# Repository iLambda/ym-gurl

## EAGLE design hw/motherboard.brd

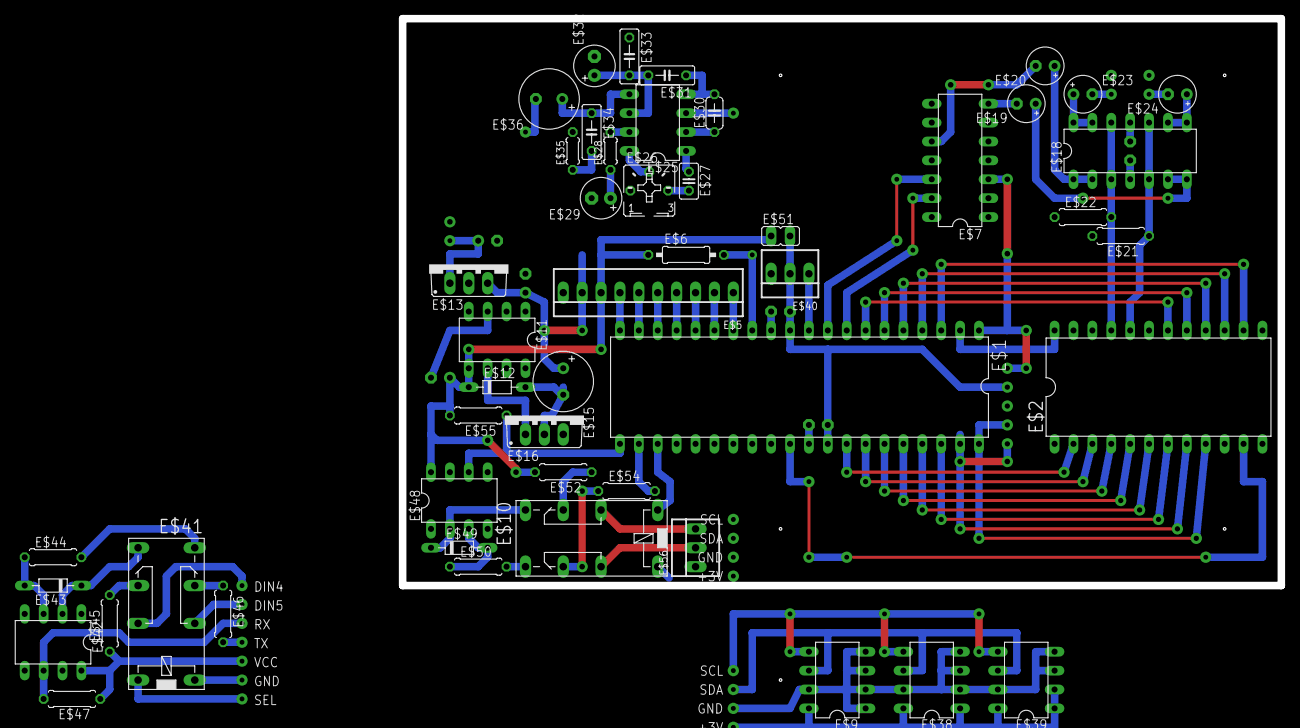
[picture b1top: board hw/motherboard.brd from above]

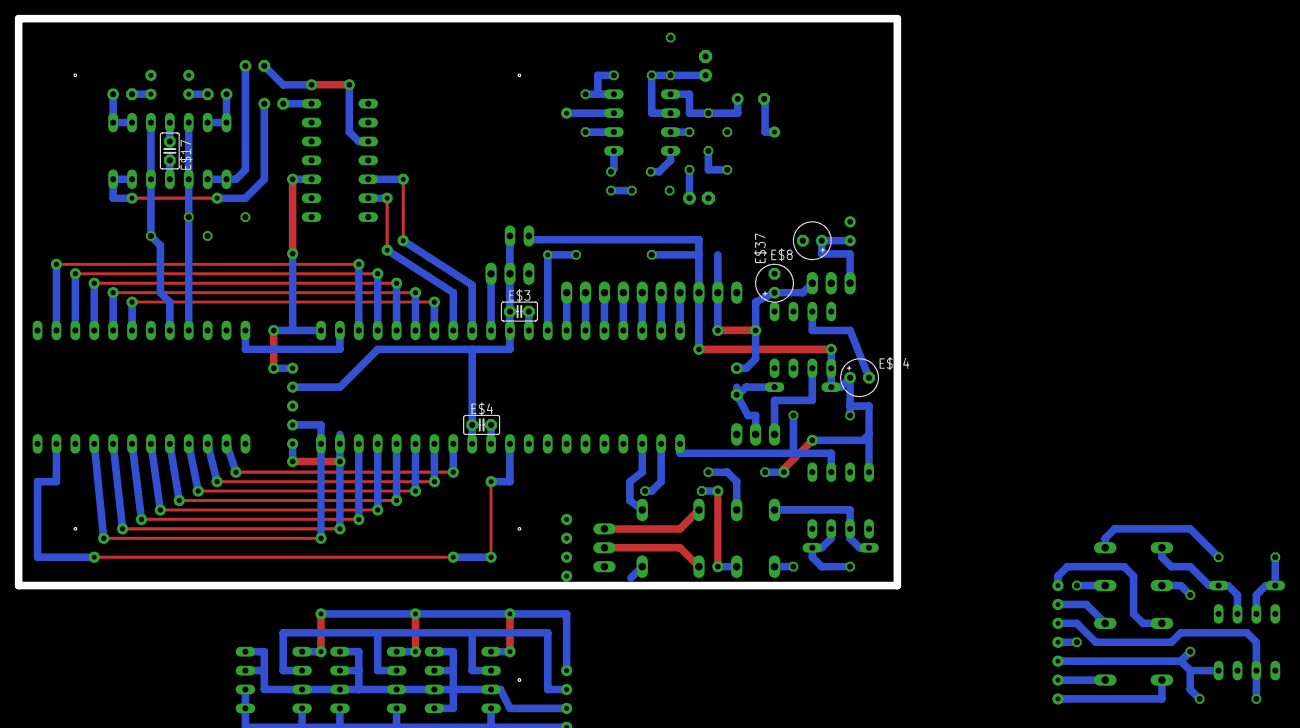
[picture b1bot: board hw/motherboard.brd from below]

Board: 2 copper layers, 118.1 x 76.2 mm, 55 parts (6 on the bottom side), 73 nets.

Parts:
E$1: DIL40
E$2: DIL24-6
E$3, E$4, E$17: C2.5-2
E$5: 22-23-2101
E$6: 0207/10
E$7, E$18: DIL14
E$8, E$14, E$19, E$20, E$23, E$24, E$37: E2,5-5
E$9, E$11, E$25, E$38, E$39, E$42, E$48: DIL08
E$10, E$41: 351
E$12, E$43, E$49: D-7.5
E$13, E$16: TO220V
E$15, E$36: E3,5-8
E$21, E$22, E$44, E$45, E$46, E$47, E$50, E$52, E$54, E$55: 0207/7
E$26: B25P
E$27: C025-025X050
E$28, E$35: 0204/5
E$29, E$32: E2,5-6
E$30: C050-024X044
E$31, E$33, E$34: C050-025X075
E$40, E$56: 22-23-2031
E$51: JP1

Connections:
+3V: E$5.9, E$13.3, E$15.+, E$37.+
+5V: E$5.8, E$6.1, E$11.5, E$12.C, E$14.+, E$48.8, E$51.1, E$52.2, E$55.2
+5V_JMP: E$1.11, E$1.32, E$3.1, E$40.2, E$51.2
GND: E$1.12, E$1.31, E$2.1, E$2.19, E$3.2, E$4.2, E$5.10, E$7.1, E$7.4, E$7.6, E$7.9, E$7.11, E$8.-, E$10.16, E$11.1, E$11.3, E$11.7, E$13.2, E$14.-, E$16.3, E$17.1, E$18.11, E$21.2, E$22.1, E$37.-, E$40.3, E$48.5, E$56.1
S$1: E$7.10, E$20.-
S$2: E$9.8, E$38.1, E$38.8, E$39.1, E$39.2, E$39.8
S$7: E$1.39, E$2.8
S$8: E$1.40, E$2.9
S$9: E$1.33, E$2.2
S$10: E$1.34, E$2.3
S$11: E$1.35, E$2.4
S$12: E$1.36, E$2.5
S$13: E$1.37, E$2.6
S$14: E$1.38, E$2.7
S$15: E$1.14, E$5.1
S$19: E$1.3, E$2.14
S$20: E$1.2, E$2.24
S$22: E$9.5, E$38.5, E$39.5
S$26: E$1.4, E$2.15
S$27: E$1.5, E$2.16
S$28: E$1.6, E$2.17
S$29: E$1.7, E$2.18
S$30: E$1.10, E$40.1
S$35: E$41.O2, E$45.2
S$36: E$1.15, E$5.2
S$37: E$1.16, E$5.3
S$38: E$1.17, E$5.4
S$39: E$1.18, E$5.5
S$40: E$1.19, E$5.6
S$41: E$1.20, E$5.7
S$42: E$1.13, E$6.2
S$43: E$1.21, E$48.6, E$55.1
S$44: E$42.8, E$45.1, E$47.1
S$45: E$41.O1, E$46.1
S$47: E$41.S2, E$42.2, E$43.C
S$49: E$48.3, E$49.A, E$50.1
S$50: E$42.3, E$43.A, E$44.1
S$52: E$10.S1, E$48.2, E$49.C
S$53: E$1.22, E$54.2
S$55: E$1.30, E$2.11
S$56: E$10.S2, E$50.2
S$57: E$41.S1, E$44.2
S$59: E$10.O2, E$54.1
S$63: E$12.A, E$15.-, E$16.2
S$64: E$42.6, E$47.2
S$65: E$1.23, E$10.1
S$66: E$10.P1, E$56.3
S$67: E$10.P2, E$56.2
S$68: E$9.1, E$9.2, E$9.3, E$9.4, E$9.7, E$38.2, E$38.3, E$38.4, E$38.7, E$39.3, E$39.4, E$39.7
S$69: E$10.O1, E$52.1
S$70: E$11.6, E$16.1
S$73: E$18.13, E$18.14, E$23.+
S$74: E$18.1, E$18.2, E$20.+
S$75: E$18.8, E$18.9, E$24.+
S$77: E$1.8, E$7.13
S$78: E$1.9, E$7.12
S$79: E$25.8, E$26.S
S$80: E$1.1, E$7.3
S$82: E$7.7, E$19.-
S$83: E$26.E, E$27.2
S$84: E$2.21, E$18.3, E$18.12, E$22.2
S$85: E$2.20, E$18.5, E$18.10, E$21.1
S$87: E$17.2, E$18.4
S$89: E$18.6, E$18.7, E$19.+
S$93: E$25.7, E$28.2
S$94: E$28.1, E$29.+
S$96: E$25.4, E$30.2, E$31.1
S$97: E$25.2, E$30.1
S$99: E$25.5, E$34.1, E$36.+
S$100: E$25.1, E$27.1
S$101: E$25.6, E$31.2, E$32.+, E$33.2
S$102: E$34.2, E$35.1
S$104: E$8.+, E$13.1

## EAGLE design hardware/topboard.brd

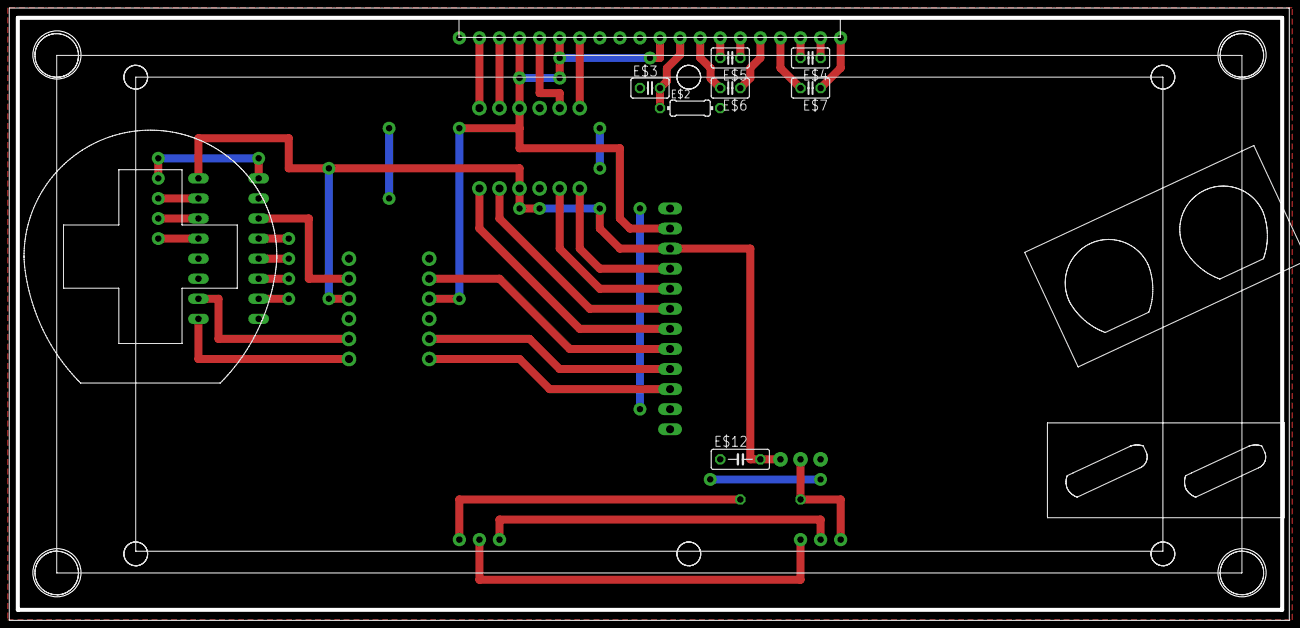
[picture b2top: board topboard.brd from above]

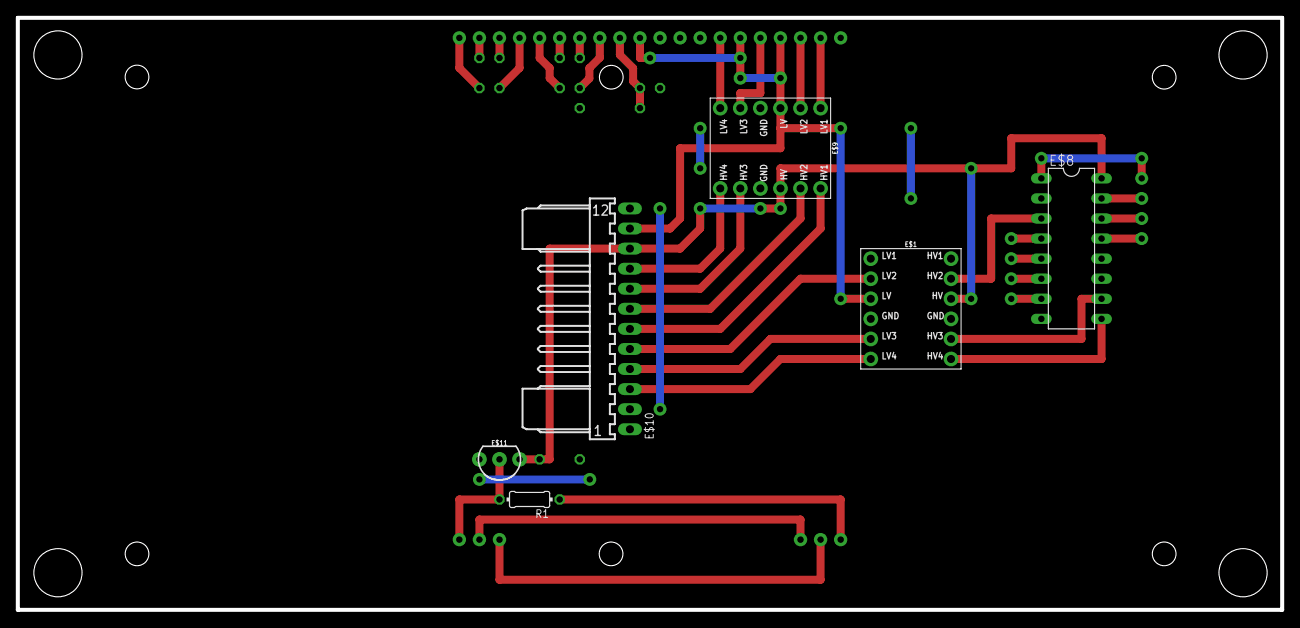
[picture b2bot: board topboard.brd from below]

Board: 2 copper layers, 160.0 x 74.9 mm, 13 parts (6 on the bottom side), 15 nets.

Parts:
E$1, E$9: SPARKFUN_LOGIC_LEVEL_CONVERTER
E$2: 0204/7
E$3, E$4, E$5, E$6, E$7: C025-025X050
E$8: DIL16
E$10: 7395-12
E$11: TO-92-AMMO
E$12: C050-025X075
R1: 0204/7

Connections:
+3V: E$1.LV, E$9.LV, E$10.11
+5V: E$1.HV, E$8.16, E$9.HV, E$10.10, E$11.1, E$12.2
CD_3V: E$9.HV4, E$10.9
CS_3V: E$9.HV3, E$10.8
GND: E$1.GND1, E$1.GND2, E$2.2, E$3.1, E$8.8, E$9.GND1, E$9.GND2, E$10.12, E$11.3, E$12.1
RCLK: E$1.HV4, E$8.9
RCLK_3V: E$1.LV4, E$10.3
S$1: E$2.1, E$3.2
S$6: E$11.2, R1.2
SCK_3V: E$9.HV2, E$10.7
SDO_3V: E$9.HV1, E$10.6
SER: E$1.HV2, E$8.3
SER_3V: E$1.LV2, E$10.5
SRCLK: E$1.HV3, E$8.10
SRCLK_3V: E$1.LV3, E$10.4

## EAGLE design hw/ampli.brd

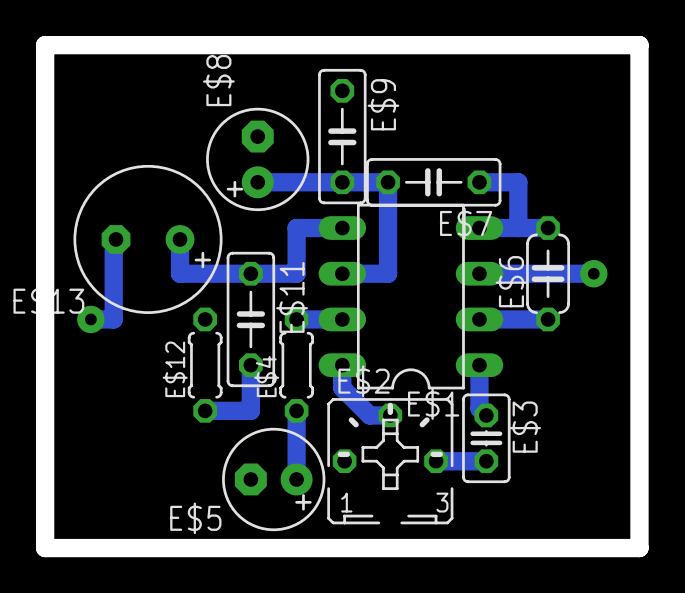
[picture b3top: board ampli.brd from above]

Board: 2 copper layers, 33.0 x 27.9 mm, 12 parts (0 on the bottom side), 10 nets.

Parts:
E$1: DIL08
E$2: B25P
E$3: C025-025X050
E$4, E$12: 0204/5
E$5, E$8: E2,5-6
E$6: C050-024X044
E$7, E$9, E$11: C050-025X075
E$13: E3,5-8

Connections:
S$1: E$1.8, E$2.S
S$2: E$2.E, E$3.2
S$3: E$1.1, E$3.1
S$4: E$1.7, E$4.2
S$5: E$4.1, E$5.+
S$6: E$1.4, E$6.2, E$7.1
S$7: E$1.2, E$6.1
S$9: E$11.2, E$12.1
S$10: E$1.5, E$11.1, E$13.+
S$11: E$1.6, E$7.2, E$8.+, E$9.2

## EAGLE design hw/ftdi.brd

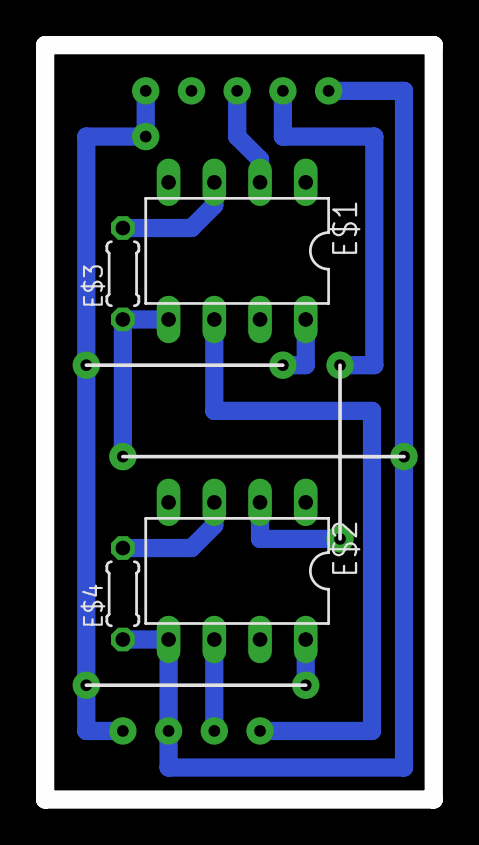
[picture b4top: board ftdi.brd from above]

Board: 2 copper layers, 21.6 x 41.9 mm, 4 parts (0 on the bottom side), 4 nets.

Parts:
E$1, E$2: DIL08
E$3, E$4: 0204/5

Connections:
S$1: E$2.3, E$4.2
S$3: E$1.5, E$3.1
S$4: E$1.3, E$3.2
S$14: E$2.5, E$4.1

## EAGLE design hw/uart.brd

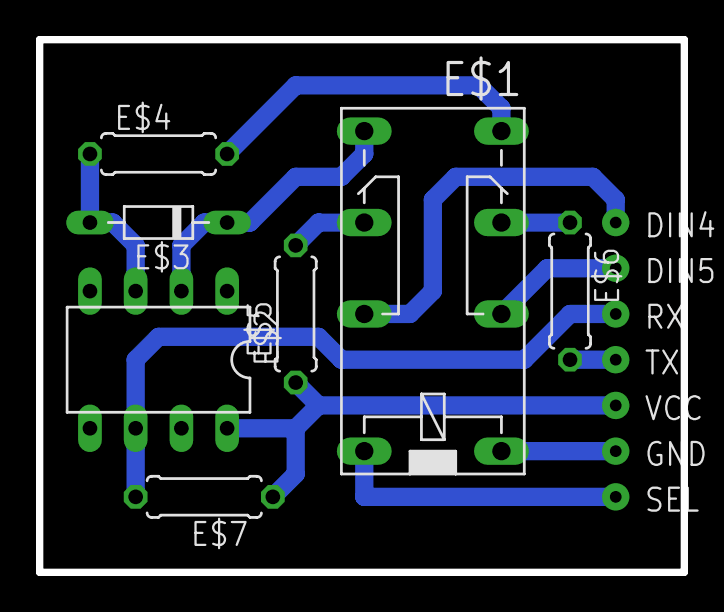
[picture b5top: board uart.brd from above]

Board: 2 copper layers, 35.8 x 29.6 mm, 7 parts (0 on the bottom side), 7 nets.

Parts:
E$1: 351
E$2: DIL08
E$3: D-7.5
E$4, E$5, E$6, E$7: 0207/7

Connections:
S$2: E$1.O2, E$5.2
S$4: E$2.8, E$5.1, E$7.1
S$5: E$1.S2, E$2.2, E$3.C
S$6: E$1.S1, E$4.2
S$7: E$1.O1, E$6.1
S$12: E$2.3, E$3.A, E$4.1
S$14: E$2.6, E$7.2

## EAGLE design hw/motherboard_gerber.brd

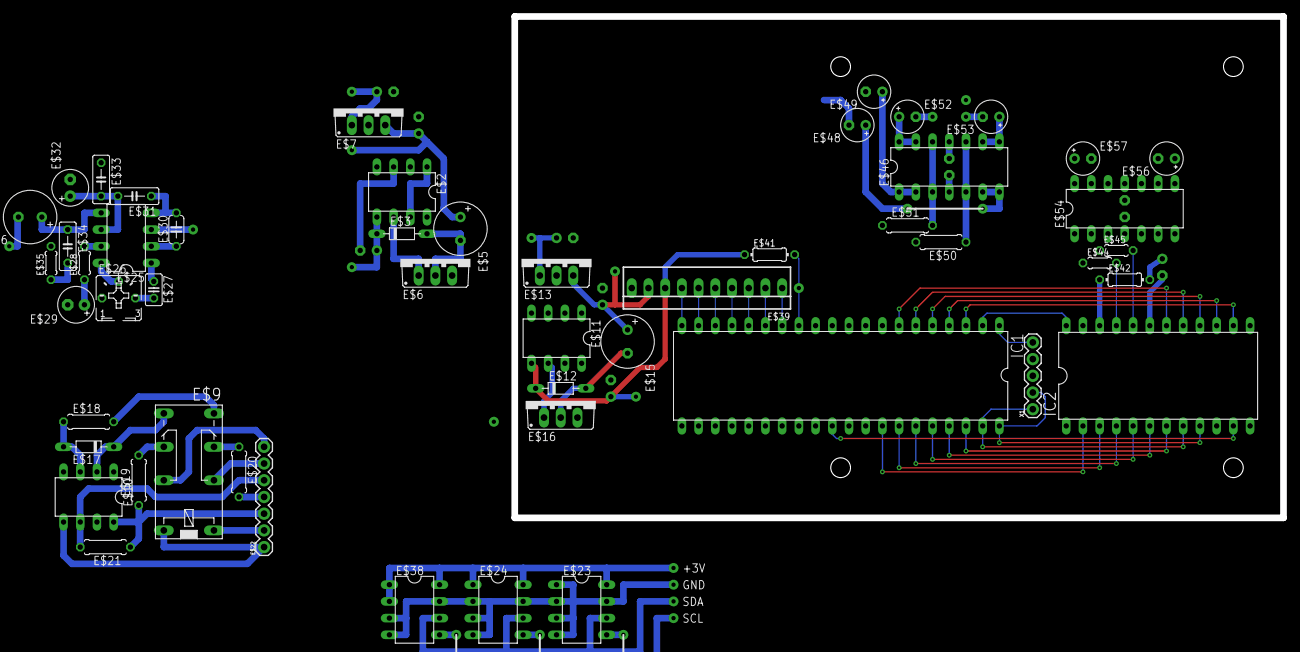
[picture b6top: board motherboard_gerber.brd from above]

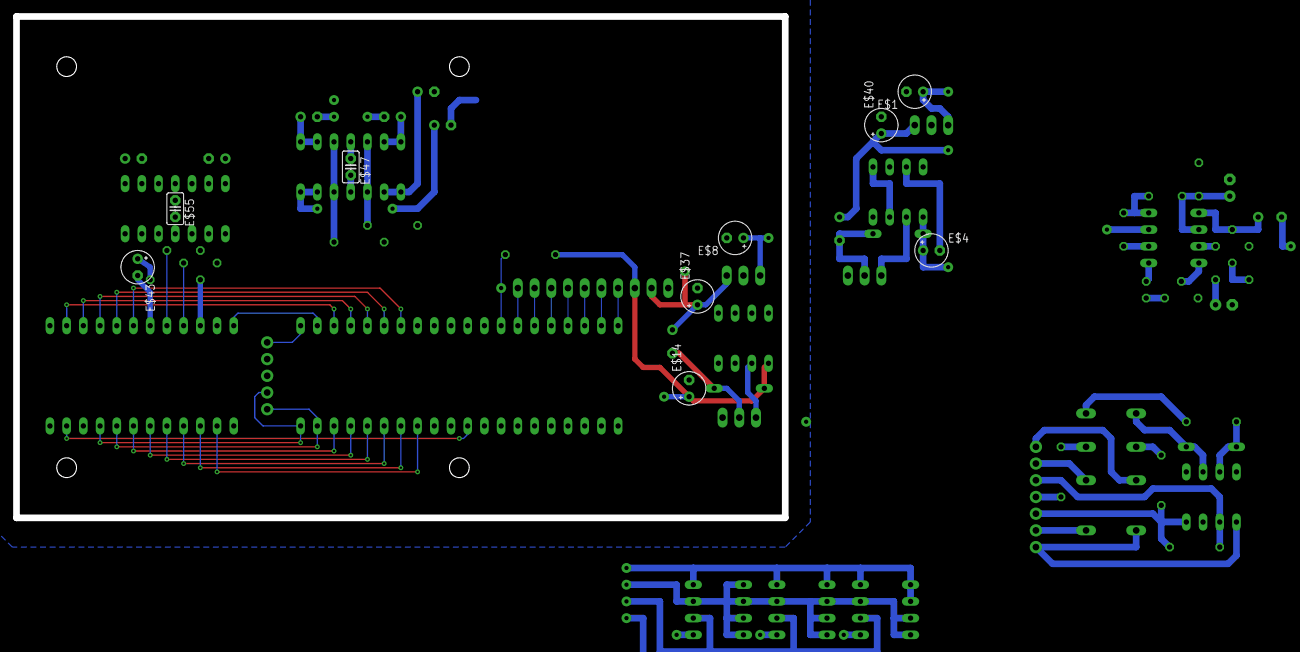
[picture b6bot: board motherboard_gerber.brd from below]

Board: 2 copper layers, 116.8 x 76.2 mm, 60 parts (9 on the bottom side), 79 nets.

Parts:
E$1, E$4, E$8, E$14, E$37, E$40, E$43, E$48, E$49, E$52, E$53, E$56, E$57: E2,5-5
E$2, E$10, E$11, E$23, E$24, E$25, E$38: DIL08
E$3, E$12, E$17: D-7.5
E$5, E$15, E$36: E3,5-8
E$6, E$7, E$13, E$16: TO220V
E$9: 351
E$18, E$19, E$20, E$21, E$50, E$51: 0207/7
E$22: 1X07
E$26: B25P
E$27: C025-025X050
E$28, E$35, E$44, E$45: 0204/5
E$29, E$32: E2,5-6
E$30: C050-024X044
E$31, E$33, E$34: C050-025X075
E$39: 22-23-2101
E$41, E$42: 0204/7
E$46, E$54: DIL14
E$47, E$55: C2.5-2
IC1: DIL40
IC2: DIL24-6
X1: 1X05

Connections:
+3V: E$13.3, E$15.+, E$37.+, E$39.9
+5V: E$11.5, E$12.C, E$14.+, E$39.8, E$41.1
GND: E$8.-, E$11.1, E$11.3, E$11.7, E$13.2, E$14.-, E$16.3, E$37.-, E$39.10, E$43.-, E$44.1, E$45.1, E$54.11, E$55.1, IC2.19
S$2: IC1.3, IC2.14
S$3: IC1.4, IC2.15
S$4: IC1.5, IC2.16
S$5: IC1.6, IC2.17
S$6: IC1.7, IC2.18
S$8: IC1.2, IC2.24
S$11: IC1.38, IC2.7
S$12: IC1.37, IC2.6
S$13: IC1.36, IC2.5
S$14: IC1.35, IC2.4
S$15: IC1.34, IC2.3
S$16: IC1.33, IC2.2
S$17: IC1.30, IC2.11
S$18: IC1.1, X1.5
S$19: IC1.40, IC2.9, X1.2
S$20: IC1.39, IC2.8, X1.1
S$21: E$5.+, E$7.3, E$40.+
S$22: E$9.16, E$10.5, E$22.1
S$23: E$20.2, E$22.4
S$24: E$9.P2, E$22.7
S$25: E$23.8, E$24.1, E$24.8, E$38.2, E$38.8
S$26: E$9.1, E$22.2
S$27: E$9.P1, E$22.6
S$28: E$9.S2, E$10.2, E$17.C
S$29: E$10.3, E$17.A, E$18.1
S$30: E$10.6, E$21.2, E$22.5
S$31: E$10.8, E$19.1, E$21.1, E$22.3
S$32: E$9.O2, E$19.2
S$33: E$9.S1, E$18.2
S$34: E$9.O1, E$20.1
S$44: E$24.3, E$24.4, E$38.3, E$38.4, E$38.7
S$45: E$23.1, E$23.3, E$23.4
S$46: E$39.7, IC1.20
S$47: E$41.2, IC1.13
S$48: E$12.A, E$15.-, E$16.2
S$49: E$39.6, IC1.19
S$50: E$11.6, E$16.1
S$51: E$39.5, IC1.18
S$52: E$39.4, IC1.17
S$53: E$39.3, IC1.16
S$54: E$39.2, IC1.15
S$55: E$39.1, IC1.14
S$56: E$42.1, IC2.22
S$57: E$42.2, E$43.+
S$58: E$44.2, E$54.3, E$54.12, IC2.21
S$59: E$45.2, E$54.5, E$54.10, IC2.20
S$60: E$54.6, E$54.7
S$61: E$54.1, E$54.2
S$62: E$54.13, E$54.14, E$57.+
S$63: E$54.8, E$54.9, E$56.+
S$64: E$54.4, E$55.2
S$65: E$2.5, E$3.C
S$66: E$3.A, E$5.-, E$6.2
S$67: E$2.3, E$4.-
S$68: E$2.1, E$2.7
S$70: E$2.6, E$6.1
S$73: E$46.13, E$46.14, E$52.+
S$74: E$46.1, E$46.2, E$49.+
S$75: E$46.8, E$46.9, E$53.+
S$79: E$25.8, E$26.S
S$83: E$26.E, E$27.2
S$84: E$46.3, E$46.12, E$51.2
S$85: E$46.5, E$46.10, E$50.1
S$86: E$46.11, E$47.1
S$87: E$46.4, E$47.2
S$89: E$46.6, E$46.7
S$93: E$25.7, E$28.2
S$94: E$28.1, E$29.+
S$96: E$25.4, E$30.2, E$31.1
S$97: E$25.2, E$30.1
S$99: E$25.5, E$34.1, E$36.+
S$100: E$25.1, E$27.1
S$101: E$25.6, E$31.2, E$32.+, E$33.2
S$102: E$34.2, E$35.1
S$104: E$1.+, E$7.1
VIN: E$8.+, E$13.1

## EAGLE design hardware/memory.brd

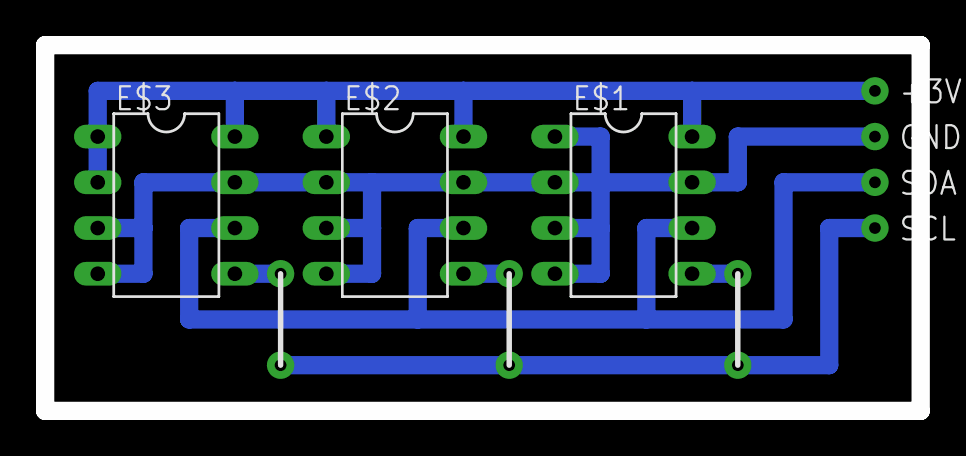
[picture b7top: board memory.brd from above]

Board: 2 copper layers, 48.6 x 20.3 mm, 3 parts (0 on the bottom side), 3 nets.

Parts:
E$1, E$2, E$3: DIL08

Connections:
S$1: E$1.8, E$2.1, E$2.8, E$3.2, E$3.8
S$3: E$1.1, E$1.3, E$1.4
S$16: E$2.3, E$2.4, E$3.3, E$3.4, E$3.7

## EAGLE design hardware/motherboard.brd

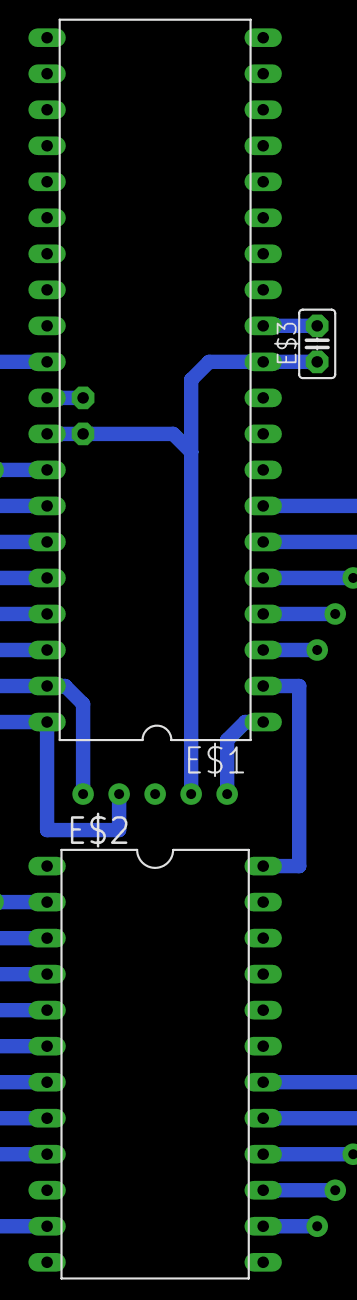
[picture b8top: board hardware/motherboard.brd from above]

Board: 2 copper layers, 4 parts (1 on the bottom side), 4 nets.

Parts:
E$1: DIL40
E$2: DIL24-6
E$3, E$4: C2.5-2

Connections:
S$16: E$1.31, E$4.2
S$20: E$1.2, E$2.24
S$31: E$1.11, E$1.32, E$3.1
S$34: E$1.12, E$3.2

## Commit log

2019-05-01 Added source
2019-05-06 Added hardware
2019-10-20 Rewrote fw for stm32, using a nucleo f746zg
2019-10-20 Fixed setLEDs
2019-10-20 Added bootscreen as an example
2019-10-20 Test on ST7920
2019-10-20 Edited example
2019-10-20 Added topboards
2019-10-20 Moved topbards into hw/
2019-10-21 Display specific u8g2 libraries are now declared extern C. Implemented SPI HW procedure
2019-10-21 Display is now a static class ; since the methods are all thread (and ISR) safe, no pointer to carry around is simpler
2019-10-21 Added thread priority in Display
2019-10-21 Implemented controller
2019-10-21 Started implementing read() operation
2019-10-21 Added Event (multitarget callbacks) helper
2019-10-21 Refactored Controller code
2019-10-21 Refactored audio manager. Controller init added in main
2019-10-21 Renamed ui/ folder to img/ folder to avoid confusions with ui:: namespace
2019-10-22 Removed ui/ folder
2019-10-22 Highly experimental midi implementation. Do not run, test before.
2019-10-22 Implemented better midi thread.
2019-10-22 Added midimode ; select btwn MIDI_IN and MIDI_OUT
2019-10-25 Added an implementation for a doubly linked list
2019-10-27 Added range_t helper
2019-10-27 Added images and script to export as XBM
2019-10-27 Fixed erasing all screens on run()
2019-10-27 Edited main
2019-10-27 Fixed compile-time bugs in controller
2019-10-27 Added images
2019-10-27 Added frame rendering routine
2019-10-28 Added filename capture
2019-10-28 Removed incoherent tty baud rate
2019-10-28 Fixed bugs in dllist
2019-10-28 Debug uart now uses RawSerial
2019-10-28 Added battery charging in Controller state
2019-10-28 MIDI driver RawSerial is not statically initialized anymore. Only starts when controller is run
2019-10-28 Added fsm_t datastructure for small table fsm
2019-10-28 Removed useless comment abt controller initialization
2019-10-29 Fix intellisense bug
2019-10-29 Fixed wait_ms deprecation

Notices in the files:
parts and their libraries:
SparkFun-Boards: Licensing: Creative Commons ShareAlike 4.0 International - https://creativecommons.org/licenses/by-sa/4.0
